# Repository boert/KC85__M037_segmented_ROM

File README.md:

# KC85__M037_segmented_ROM
Modul für den KC85/3/4/5: Segmentierter ROM in den Größen 32/64/128 kByte

optionale Bedienoberfläche

## Verzeichnisübersicht

Verzeichnis             | Inhalt
-----------             | ------
Platine                 | Schaltplan, Layout und Stückliste/BOM
EPROM-Images            | vorgefertigt, für Emulator und EPROM-Brenner
Generator-Software      | um eigene EPROM-Images zu erstellen (C++, Qt5)
ROMSTART                | Menüsoftware, die auf dem Modul läuft (Z80-Assembler)

## Credits

Dieses Projekt nutzt u.a. folgende Software:
- KiCad, https://www.kicad.org/
- pasmo, https://pasmo.speccy.org/
- Python, https://www.python.org/
- Qt, https://www.qt.io/
- ZX7, https://spectrumcomputing.co.uk/entry/27996/ZX-Spectrum/ZX7

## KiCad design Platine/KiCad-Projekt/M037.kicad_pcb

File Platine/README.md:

# Unterlagen zur Leiterplatte

Dokument            | Verweis
--------            | -------
Schaltplan          | [M037_Schaltplan.pdf](https://raw.githubusercontent.com/boert/KC85__M037_segmented_ROM/main/Platine/M037_Schaltplan.pdf)
Layout              | [M037_Platine.pdf](https://raw.githubusercontent.com/boert/KC85__M037_segmented_ROM/main/Platine/M037_Platine.pdf)
Stückliste/BOM      | [M037_Stueckliste.xls](https://raw.githubusercontent.com/boert/KC85__M037_segmented_ROM/main/Platine/M037_Stueckliste.xls)
Bestückungshilfe    | [M037_Bestueckhilfe.html](https://raw.githubusercontent.com/boert/KC85__M037_segmented_ROM/main/Platine/M037_Bestueckhilfe.html)

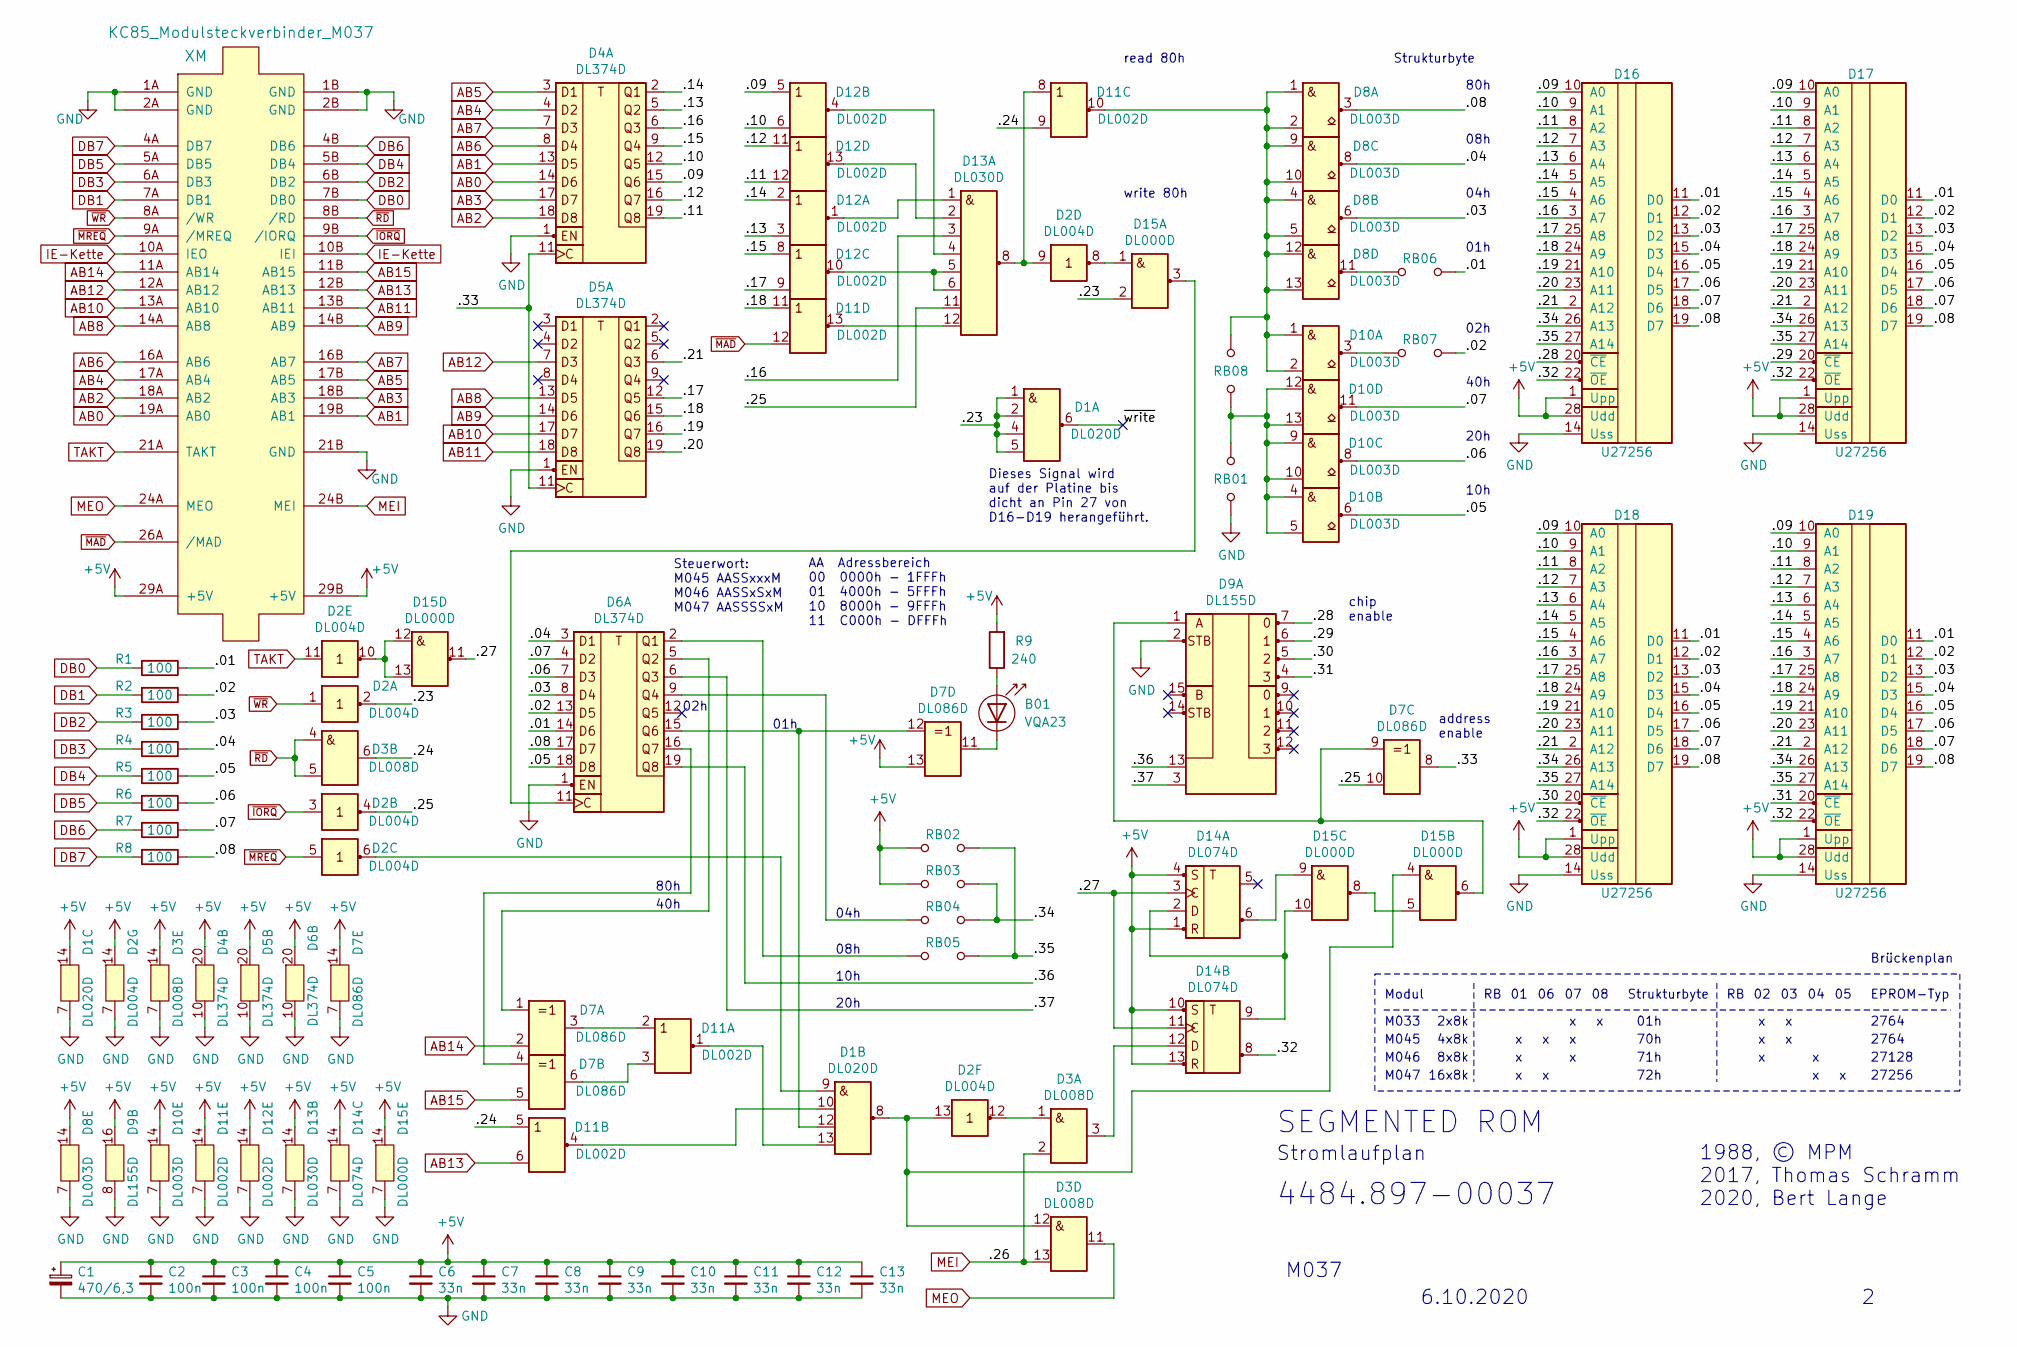
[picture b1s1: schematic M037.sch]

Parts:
B01: VQA23; LED_D5.0mm_Horizontal_O3.81mm_Z3.0mm
C1: 470/6,3; CP_Axial_L21.0mm_D10.0mm_P25.0mm...35.0mm_Horizontal
C2, C3, C4, C5: 100n; C_Disc_D8.0mm_W2.0mm_P5.00mm_P7.50mm
C6, C7, C8, C9, C10, C11, C12, C13: 33n; C_Disc_D8.0mm_W2.0mm_P5.00mm_P7.50mm
D1: DL020D; DIP-14_W7.62mm_Socket_LongPads
D2: DL004D; DIP-14_W7.62mm_Socket_LongPads
D3: DL008D; DIP-14_W7.62mm_Socket_LongPads
D4, D5, D6: DL374D; DIP-20_W7.62mm_Socket_LongPads
D7: DL086D; DIP-14_W7.62mm_Socket_LongPads
D8, D10: DL003D; DIP-14_W7.62mm_Socket_LongPads
D9: DL155D; DIP-16_W7.62mm_Socket_LongPads
D11, D12: DL002D; DIP-14_W7.62mm_Socket_LongPads
D13: DL030D; DIP-14_W7.62mm_Socket_LongPads
D14: DL074D; DIP-14_W7.62mm_Socket_LongPads
D15: DL000D; DIP-14_W7.62mm_Socket_LongPads
D16, D17, D18, D19: U27256; DIP-28_W15.24mm_Socket_LongPads
R1, R2, R3, R4, R5, R6, R7, R8: 100; R_Axial_L6.3mm_D2.0mm_P10.16mm_Horizontal
R9: 240; R_Axial_DIN0207_L6.3mm_D2.5mm_P10.16mm_Horizontal
RB01, RB02, RB03, RB04, RB05, RB06, RB07, RB08: Brücke; TestPoint_2Pads_Pitch2.54mm_Drill0.8mm
XM: KC85_Modulsteckverbinder_M037

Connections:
+5V: C1.1, C2.1, C3.1, C4.1, C5.1, C6.1, C7.1, C8.1, C9.1, C10.1, C11.1, C12.1, C13.1, D1.14 (Vcc), D2.14 (Vcc), D3.14 (Vcc), D4.20 (Vcc), D5.20 (Vcc), D6.20 (Vcc), D7.13 (B4), D7.14 (Vcc), D8.14 (Vcc), D9.16 (Vcc), D10.14 (Vcc), D11.14 (Vcc), D12.14 (Vcc), D13.14 (Vcc), D14.1 (R1), D14.4 (S1), D14.10 (S2), D14.13 (R2), D14.14 (Vcc), D15.14 (Vcc), D16.1 (Upp), D16.28 (Udd), D17.1 (Upp), D17.28 (Udd), D18.1 (Upp), D18.28 (Udd), D19.1 (Upp), D19.28 (Udd), R9.2, RB02.1, RB03.1, XM.29A (+5V), XM.29B (+5V); also elsewhere on the board
/.01: D6.14 (D6), D16.11 (D0), D17.11 (D0), D18.11 (D0), D19.11 (D0), R1.1, RB06.2
/.02: D6.13 (D5), D16.12 (D1), D17.12 (D1), D18.12 (D1), D19.12 (D1), R2.1, RB07.2
/.03: D6.8 (D4), D8.6 (Y2), D16.13 (D2), D17.13 (D2), D18.13 (D2), D19.13 (D2), R3.1
/.04: D6.3 (D1), D8.8 (Y3), D16.15 (D3), D17.15 (D3), D18.15 (D3), D19.15 (D3), R4.1
/.05: D6.18 (D8), D10.6 (Y2), D16.16 (D4), D17.16 (D4), D18.16 (D4), D19.16 (D4), R5.1
/.06: D6.7 (D3), D10.8 (Y3), D16.17 (D5), D17.17 (D5), D18.17 (D5), D19.17 (D5), R6.1
/.07: D6.4 (D2), D10.11 (Y4), D16.18 (D6), D17.18 (D6), D18.18 (D6), D19.18 (D6), R7.1
/.08: D6.17 (D7), D8.3 (Y1), D16.19 (D7), D17.19 (D7), D18.19 (D7), D19.19 (D7), R8.1
/.09: D4.15 (Q6), D12.5 (A2), D16.10 (A0), D17.10 (A0), D18.10 (A0), D19.10 (A0)
/.10: D4.12 (Q5), D12.6 (B2), D16.9 (A1), D17.9 (A1), D18.9 (A1), D19.9 (A1)
/.11: D4.19 (Q8), D12.12 (B4), D16.8 (A2), D17.8 (A2), D18.8 (A2), D19.8 (A2)
/.12: D4.16 (Q7), D12.11 (A4), D16.7 (A3), D17.7 (A3), D18.7 (A3), D19.7 (A3)
/.13: D4.5 (Q2), D12.3 (B1), D16.6 (A4), D17.6 (A4), D18.6 (A4), D19.6 (A4)
/.14: D4.2 (Q1), D12.2 (A1), D16.5 (A5), D17.5 (A5), D18.5 (A5), D19.5 (A5)
/.15: D4.9 (Q4), D12.8 (A3), D16.4 (A6), D17.4 (A6), D18.4 (A6), D19.4 (A6)
/.16: D4.6 (Q3), D13.3 (C), D16.3 (A7), D17.3 (A7), D18.3 (A7), D19.3 (A7)
/.17: D5.12 (Q5), D12.9 (B3), D16.25 (A8), D17.25 (A8), D18.25 (A8), D19.25 (A8)
/.18: D5.15 (Q6), D11.11 (A4), D16.24 (A9), D17.24 (A9), D18.24 (A9), D19.24 (A9)
/.19: D5.16 (Q7), D16.21 (A10), D17.21 (A10), D18.21 (A10), D19.21 (A10)
/.20: D5.19 (Q8), D16.23 (A11), D17.23 (A11), D18.23 (A11), D19.23 (A11)
/.21: D5.6 (Q3), D16.2 (A12), D17.2 (A12), D18.2 (A12), D19.2 (A12)
/.23: D1.1 (A1), D1.2 (B1), D1.4 (C1), D1.5 (D1), D2.2 (Y1), D15.2 (B1)
/.24: D3.6 (Y2), D11.5 (A2), D11.9 (B3)
/.25: D2.4 (Y2), D7.10 (B3), D13.11 (G)
/.27: D14.3 (T1), D14.11 (T2), D15.11 (Y4)
/.28: D9.7 (1Y0), D16.20 (~CE)
/.29: D9.6 (1Y1), D17.20 (~CE)
/.30: D9.5 (1Y2), D18.20 (~CE)
/.31: D9.4 (1Y3), D19.20 (~CE)
/.32: D14.8 (/Q2), D16.22 (~OE), D17.22 (~OE), D18.22 (~OE), D19.22 (~OE)
/.33: D4.11 (C), D5.11 (C), D7.8 (Y3)
/.34: D16.26 (A13), D17.26 (A13), D18.26 (A13), D19.26 (A13), RB03.2, RB04.2
/.35: D16.27 (A14), D17.27 (A14), D18.27 (A14), D19.27 (A14), RB02.2, RB05.2
/.36: D6.19 (Q8), D9.13 (S0)
/.37: D6.6 (Q3), D9.3 (S1)
/~write: D1.6 (Y1)
AB0: D4.14 (D6), XM.19A (AB0); also elsewhere on the board
AB1: D4.13 (D5), XM.19B (AB1); also elsewhere on the board
AB2: D4.18 (D8), XM.18A (AB2); also elsewhere on the board
AB3: D4.17 (D7), XM.18B (AB3); also elsewhere on the board
AB4: D4.4 (D2), XM.17A (AB4); also elsewhere on the board
AB5: D4.3 (D1), XM.17B (AB5); also elsewhere on the board
AB6: D4.8 (D4), XM.16A (AB6); also elsewhere on the board
AB7: D4.7 (D3), XM.16B (AB7); also elsewhere on the board
AB8: D5.13 (D5), XM.14A (AB8); also elsewhere on the board
AB9: D5.14 (D6), XM.14B (AB9); also elsewhere on the board
AB10: D5.17 (D7), XM.13A (AB10); also elsewhere on the board
AB11: D5.18 (D8), XM.13B (AB11); also elsewhere on the board
AB12: D5.7 (D3), XM.12A (AB12); also elsewhere on the board
AB13: D11.6 (B2), XM.12B (AB13); also elsewhere on the board
AB14: D7.2 (B1), XM.11A (AB14); also elsewhere on the board
AB15: D7.5 (B2), XM.11B (AB15); also elsewhere on the board
DB0: R1.2, XM.7B (DB0); also elsewhere on the board
DB1: R2.2, XM.7A (DB1); also elsewhere on the board
DB2: R3.2, XM.6B (DB2); also elsewhere on the board
DB3: R4.2, XM.6A (DB3); also elsewhere on the board
DB4: R5.2, XM.5B (DB4); also elsewhere on the board
DB5: R6.2, XM.5A (DB5); also elsewhere on the board
DB6: R7.2, XM.4B (DB6); also elsewhere on the board
DB7: R8.2, XM.4A (DB7); also elsewhere on the board
GND: C1.2, C2.2, C3.2, C4.2, C5.2, C6.2, C7.2, C8.2, C9.2, C10.2, C11.2, C12.2, C13.2, D1.7 (GND), D2.7 (GND), D3.7 (GND), D4.1 (EN), D4.10 (GND), D5.1 (EN), D5.10 (GND), D6.1 (EN), D6.10 (GND), D7.7 (GND), D8.7 (GND), D9.2 (1STB), D9.8 (GND), D10.7 (GND), D11.7 (GND), D12.7 (GND), D13.7 (GND), D14.7 (GND), D15.7 (GND), D16.14 (Uss), D17.14 (Uss), D18.14 (Uss), D19.14 (Uss), RB01.1, XM.1A (GND), XM.1B (GND), XM.2A (GND), XM.2B (GND), XM.21B (GND); also elsewhere on the board
MEI: D3.2 (B1), D3.13 (B4), XM.24B (MEI); also elsewhere on the board
MEO: D3.11 (Y4), XM.24A (MEO); also elsewhere on the board
unnamed: B01.1 (K), D7.11 (Y4)
unnamed: B01.2 (A), R9.1
unnamed: D1.8 (Y2), D2.13 (A6), D3.12 (A4), D15.4 (A2)
unnamed: D1.9 (A2), D2.6 (Y3)
unnamed: D1.10 (B2), D11.4 (Y2)
unnamed: D1.12 (C2), D6.15 (Q6), D7.12 (A4)
unnamed: D1.13 (D2), D11.1 (Y1)
unnamed: D2.12 (Y6), D3.1 (A1)
unnamed: D6.2 (Q1), RB05.1
unnamed: D6.5 (Q2), D7.1 (A1)
unnamed: D6.9 (Q4), RB04.1
unnamed: D6.16 (Q7), D7.4 (A2)
unnamed: D8.11 (Y4), RB06.1
unnamed: D8.1 (A1), D8.2 (B1), D8.4 (A2), D8.5 (B2), D8.9 (A3), D8.10 (B3), D8.12 (A4), D8.13 (B4), D10.1 (A1), D10.2 (B1), D11.10 (Y3), RB08.2
unnamed: D10.3 (Y1), RB07.1
unnamed: D10.4 (A2), D10.5 (B2), D10.9 (A3), D10.10 (B3), D10.12 (A4), D10.13 (B4), RB01.2, RB08.1
unnamed: D7.3 (Y1), D11.2 (A1)
unnamed: D7.6 (Y2), D11.3 (B1)
unnamed: D2.9 (A4), D11.8 (A3), D13.8 (Y)
unnamed: D11.13 (Y4), D13.12 (H)
unnamed: D12.1 (Y1), D13.1 (A)
unnamed: D12.4 (Y2), D13.4 (D)
unnamed: D12.10 (Y3), D13.5 (E), D13.6 (F)
unnamed: D12.13 (Y4), D13.2 (B)
unnamed: D14.2 (D1), D14.9 (Q2), D15.10 (B3)
unnamed: D14.6 (/Q1), D15.9 (A3)
unnamed: D3.3 (Y1), D14.12 (D2)
unnamed: D2.8 (Y4), D15.1 (A1)
unnamed: D6.11 (C), D15.3 (Y1)
unnamed: D15.5 (B2), D15.8 (Y3)
unnamed: D7.9 (A3), D9.1 (1A), D15.6 (Y2)
unnamed: D2.10 (Y5), D15.12 (A4), D15.13 (B4)
unnamed: XM.10A (IEO), XM.10B (IEI)
TAKT: D2.11 (A5), XM.21A (TAKT); also elsewhere on the board
~IORQ: D2.3 (A2), XM.9B (/IORQ); also elsewhere on the board
~MAD: D11.12 (B4), XM.26A (/MAD); also elsewhere on the board
~MREQ: D2.5 (A3), XM.9A (/MREQ); also elsewhere on the board
~RD: D3.4 (A2), D3.5 (B2), XM.8B (/RD); also elsewhere on the board
~WR: D2.1 (A1), XM.8A (/WR); also elsewhere on the board

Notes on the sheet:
read 80h
write 80h
Dieses Signal wird auf der Platine bis dicht an Pin 27 von D16-D19 herangeführt.
chip enable
address enable
SEGMENTED ROM
Stromlaufplan
4484.897-00037
Strukturbyte
Steuerwort: M045 AASSxxxM M046 AASSxSxM M047 AASSSSxM
01h
02h
04h
08h
10h
20h
40h
80h
AA Adressbereich 00 0000h - 1FFFh 01 4000h - 5FFFh 10 8000h - 9FFFh 11 C000h - DFFFh
1988, © MPM 2017, Thomas Schramm 2020, Bert Lange
M037
6.10.2020
4x8k
8x8k
16x8k
70h
71h
72h
Brückenplan
Modul
M045
M046
M047
EPROM-Typ
2764
27128
27256
2x8k
M033

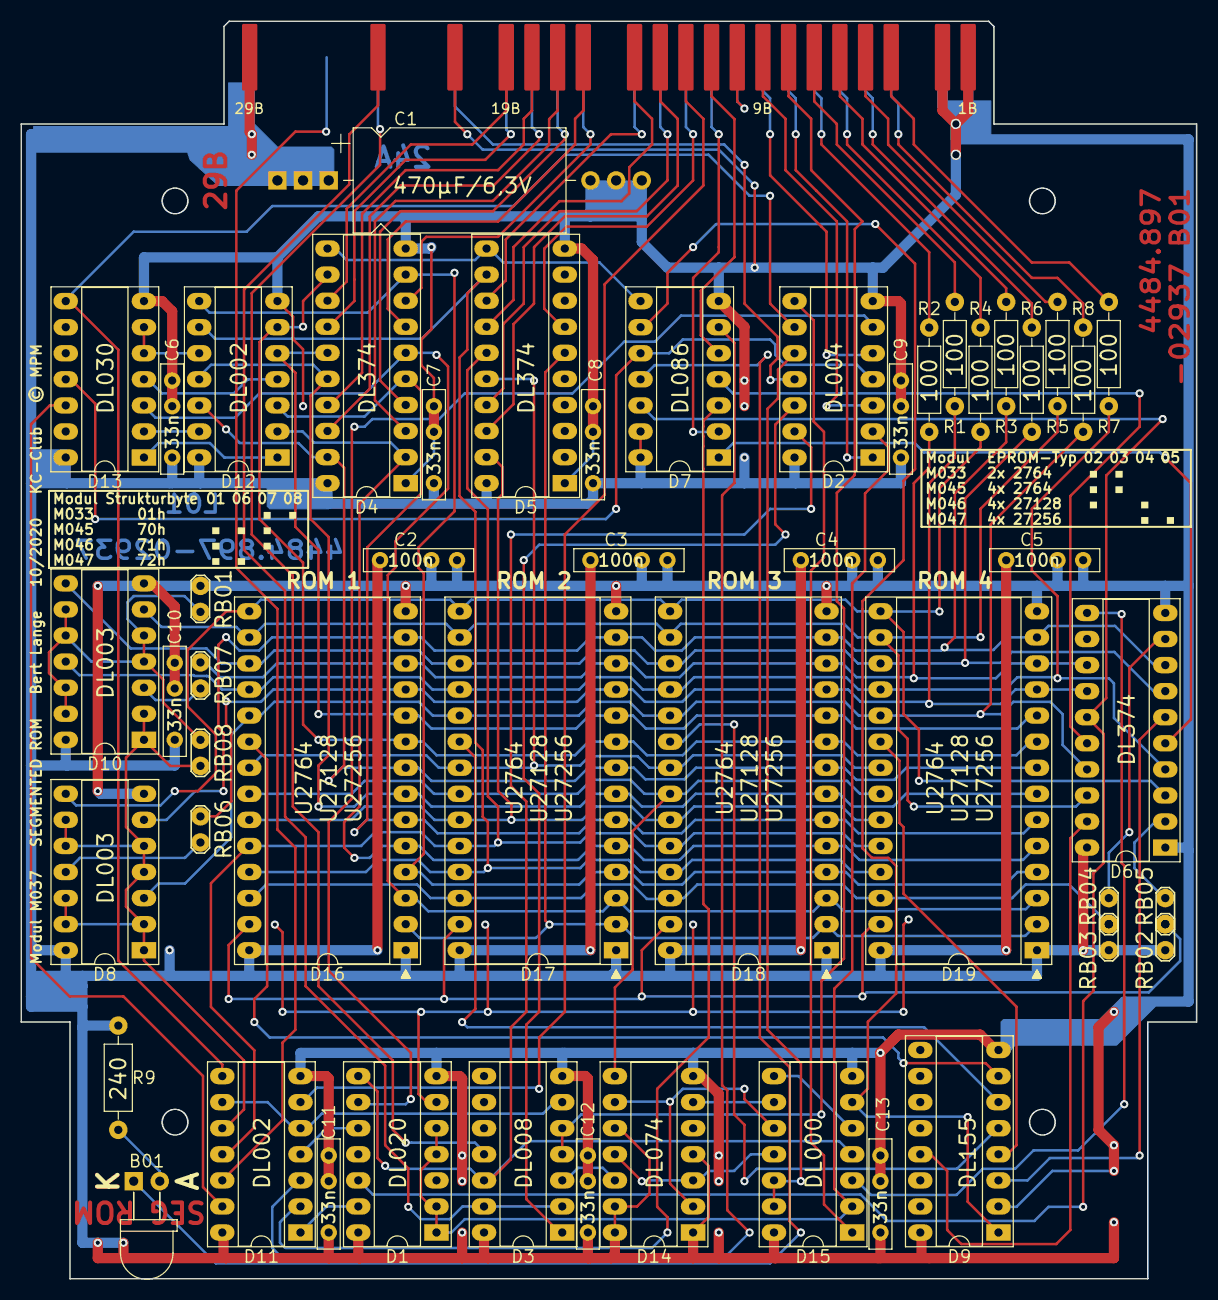
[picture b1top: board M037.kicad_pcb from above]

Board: 2 copper layers, 114.5 x 122.5 mm, 51 parts (0 on the bottom side), 102 nets.

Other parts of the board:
X1: KC85_MODULSTECKVERBINDER; KC85_Modul_M037

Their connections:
+5V: X1.29A, X1.29B; also elsewhere on the board
AB0: X1.19A; also elsewhere on the board
AB1: X1.19B; also elsewhere on the board
AB2: X1.18A; also elsewhere on the board
AB3: X1.18B; also elsewhere on the board
AB4: X1.17A; also elsewhere on the board
AB5: X1.17B; also elsewhere on the board
AB6: X1.16A; also elsewhere on the board
AB7: X1.16B; also elsewhere on the board
AB8: X1.14A; also elsewhere on the board
AB9: X1.14B; also elsewhere on the board
AB10: X1.13A; also elsewhere on the board
AB11: X1.13B; also elsewhere on the board
AB12: X1.12A; also elsewhere on the board
AB13: X1.12B; also elsewhere on the board
AB14: X1.11A; also elsewhere on the board
AB15: X1.11B; also elsewhere on the board
DB0: X1.7B; also elsewhere on the board
DB1: X1.7A; also elsewhere on the board
DB2: X1.6B; also elsewhere on the board
DB3: X1.6A; also elsewhere on the board
DB4: X1.5B; also elsewhere on the board
DB5: X1.5A; also elsewhere on the board
DB6: X1.4B; also elsewhere on the board
DB7: X1.4A; also elsewhere on the board
GND: X1.1A, X1.1B, X1.2A, X1.2B, X1.21B; also elsewhere on the board
IE-Kette: X1.10A, X1.10B
MEI: X1.24B; also elsewhere on the board
MEO: X1.24A; also elsewhere on the board
TAKT: X1.21A; also elsewhere on the board
~IORQ: X1.9B; also elsewhere on the board
~MAD: X1.26A; also elsewhere on the board
~MREQ: X1.9A; also elsewhere on the board
~RD: X1.8B; also elsewhere on the board
~WR: X1.8A; also elsewhere on the board

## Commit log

2021-09-20 erste Unterlagen
2021-09-20 update links
2021-09-20 ROMSTART hizugefügt
2021-09-20 Credits hizugefügt
2021-09-20 Generatorsoftware hinzugefügt
2021-09-20 Formatierung
2021-09-20 README.md erweitert
2021-09-20 KiCad-Projekt ergänzt
2021-09-29 Modulblende hinzugefügt
2021-09-30 add: readme
2024-04-06 fix: filename
2024-04-06 fix: color detection
2024-04-06 add: helper script
2024-04-06 add: M062
2024-04-06 change: one place for Modul-type
2024-04-06 add: support for M062
2024-04-06 add: KCC-Tools
2024-04-06 add: missing include
2024-04-06 change: simplify variables
2024-04-06 change: rename UP, restore fonts
2024-04-09 change: first M062 adoption
2024-04-09 add: target for all binarys
2024-04-09 add: M062 support
2024-04-09 add: M062 image
2024-04-15 update: screenshot
2025-02-04 add: ICONs.md
2025-02-04 fix link
2025-02-11 precise: return value
2025-02-11 fix: path
2025-02-11 remove: compile warning
2025-02-11 change: fix style
2025-02-11 add: core library

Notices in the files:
Platine/KiCad-Projekt/M037.kicad_pcb:
Modul M037 SEGMENTED ROM Bert Lange 10/2020 KC-Club © MPM
